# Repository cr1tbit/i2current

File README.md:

# I2Current powerboard

The Raison d'être of this board is to be a powerful, extensible, and affordable replacement for hotglueing a random powerbank into your next portable small-scale electronic project.

The largest benefit comes from the I2C interface - If, for example, a Raspberry Pi is powered with this board, it can actually check the battery state, if DC-jack is currently charging the device, or even see the power draw of other peripherals connected to this system.

The board is most useful for powering devices requiring peak power draw between 15W-60W.

For devices requiring less power, the cost overhead becomes a bit too much - alternative solutions on aliexpress, albeit not as much versatile, can cost less than $3 (this board costs ~$10, ordering 20 units from JLCPCB).

## Sub-components

### BQ25792 Li-Ion charger

Specs:

* 3.6-24V input, max 3A (realistically, ~60W)
* Input voltage independent from battery pack (buck-boost built-in)
* Input from USB-C and/or DC barrel jack.
* Can provide up to 3.33A@20V output to the same USB-C port
* can work with 1S-4S (cells in series)
* output current 5A (with 4 cells (~16V), up to ~80W output)
* Works properly without battery pack too (can work as buck-boost power supply)
* Many parameters configurable via i2c
* Various battery/input/output voltages/currents readout

This charger is incredibly universal, costing around 1$ it provides versatility for many types of projects.

### TPS56637 5V output step-down converter

It can provide up to 6A (30W) on output. However, it requires atleast 2S packet to be usable.

### MT2492 3V3 DC-DC

This converter supports optional built-in ESP32-C3 controller, and can also be accesed via output pins

### SPX3819M5-L-3-3 3V3 LDO

This low-power stabilizer provides power to onboard devices and some circuitry. It cannot be turned off, in contrast to 2 other converters.

### FUSB302B Power Delivery controller

This device is controlled via i2c, and can be used to negotiate up to 5A/20V from compatible USB-C chargers.

Arduino library is available.

## Connectors

### Output 2.54 connector

This connector has been designed for low-profile goldpin socket connector (the male header actually goes through the holes in the PCB)

Shield can be designed, utilizing this connector.

### Picoblade connector

This connector is dedicated for devices, where a "master" board sits somewhere else in the system. 

### Battery connector

* Battery input
* NTC resistor input (every battery pack should contain one, more on that later)
* GND
* Battery output (coming from BQ charger, provides stable voltage when baterry is depleated or missing)
* GLOB_OFF (pin for external power-off switch)
* VDC_IN (same as from barrel jack input)

## More to come...

this board has many more fun quirks - I'll describe more details at a later date.

* optional mini front panel with OLED
* Passive-PoE input
* standalone 4-channel WLED controller
* USB data lanes passthrough for 2 connectors and built-in ESP32

#### Todo - document:

* Li-ion safety guide
* USB passthrough
* GLOB_OFF usage
* Pinout description for every connector
* 1S-4S config and limitations

## Sponsors

Developent of this board is supported by [Clue.lamp](https://www.instagram.com/clue.lamp/).

Check them out, the device looks really nice, and utilizes state-of-the-art electronic design for both wired and wireless usage :)

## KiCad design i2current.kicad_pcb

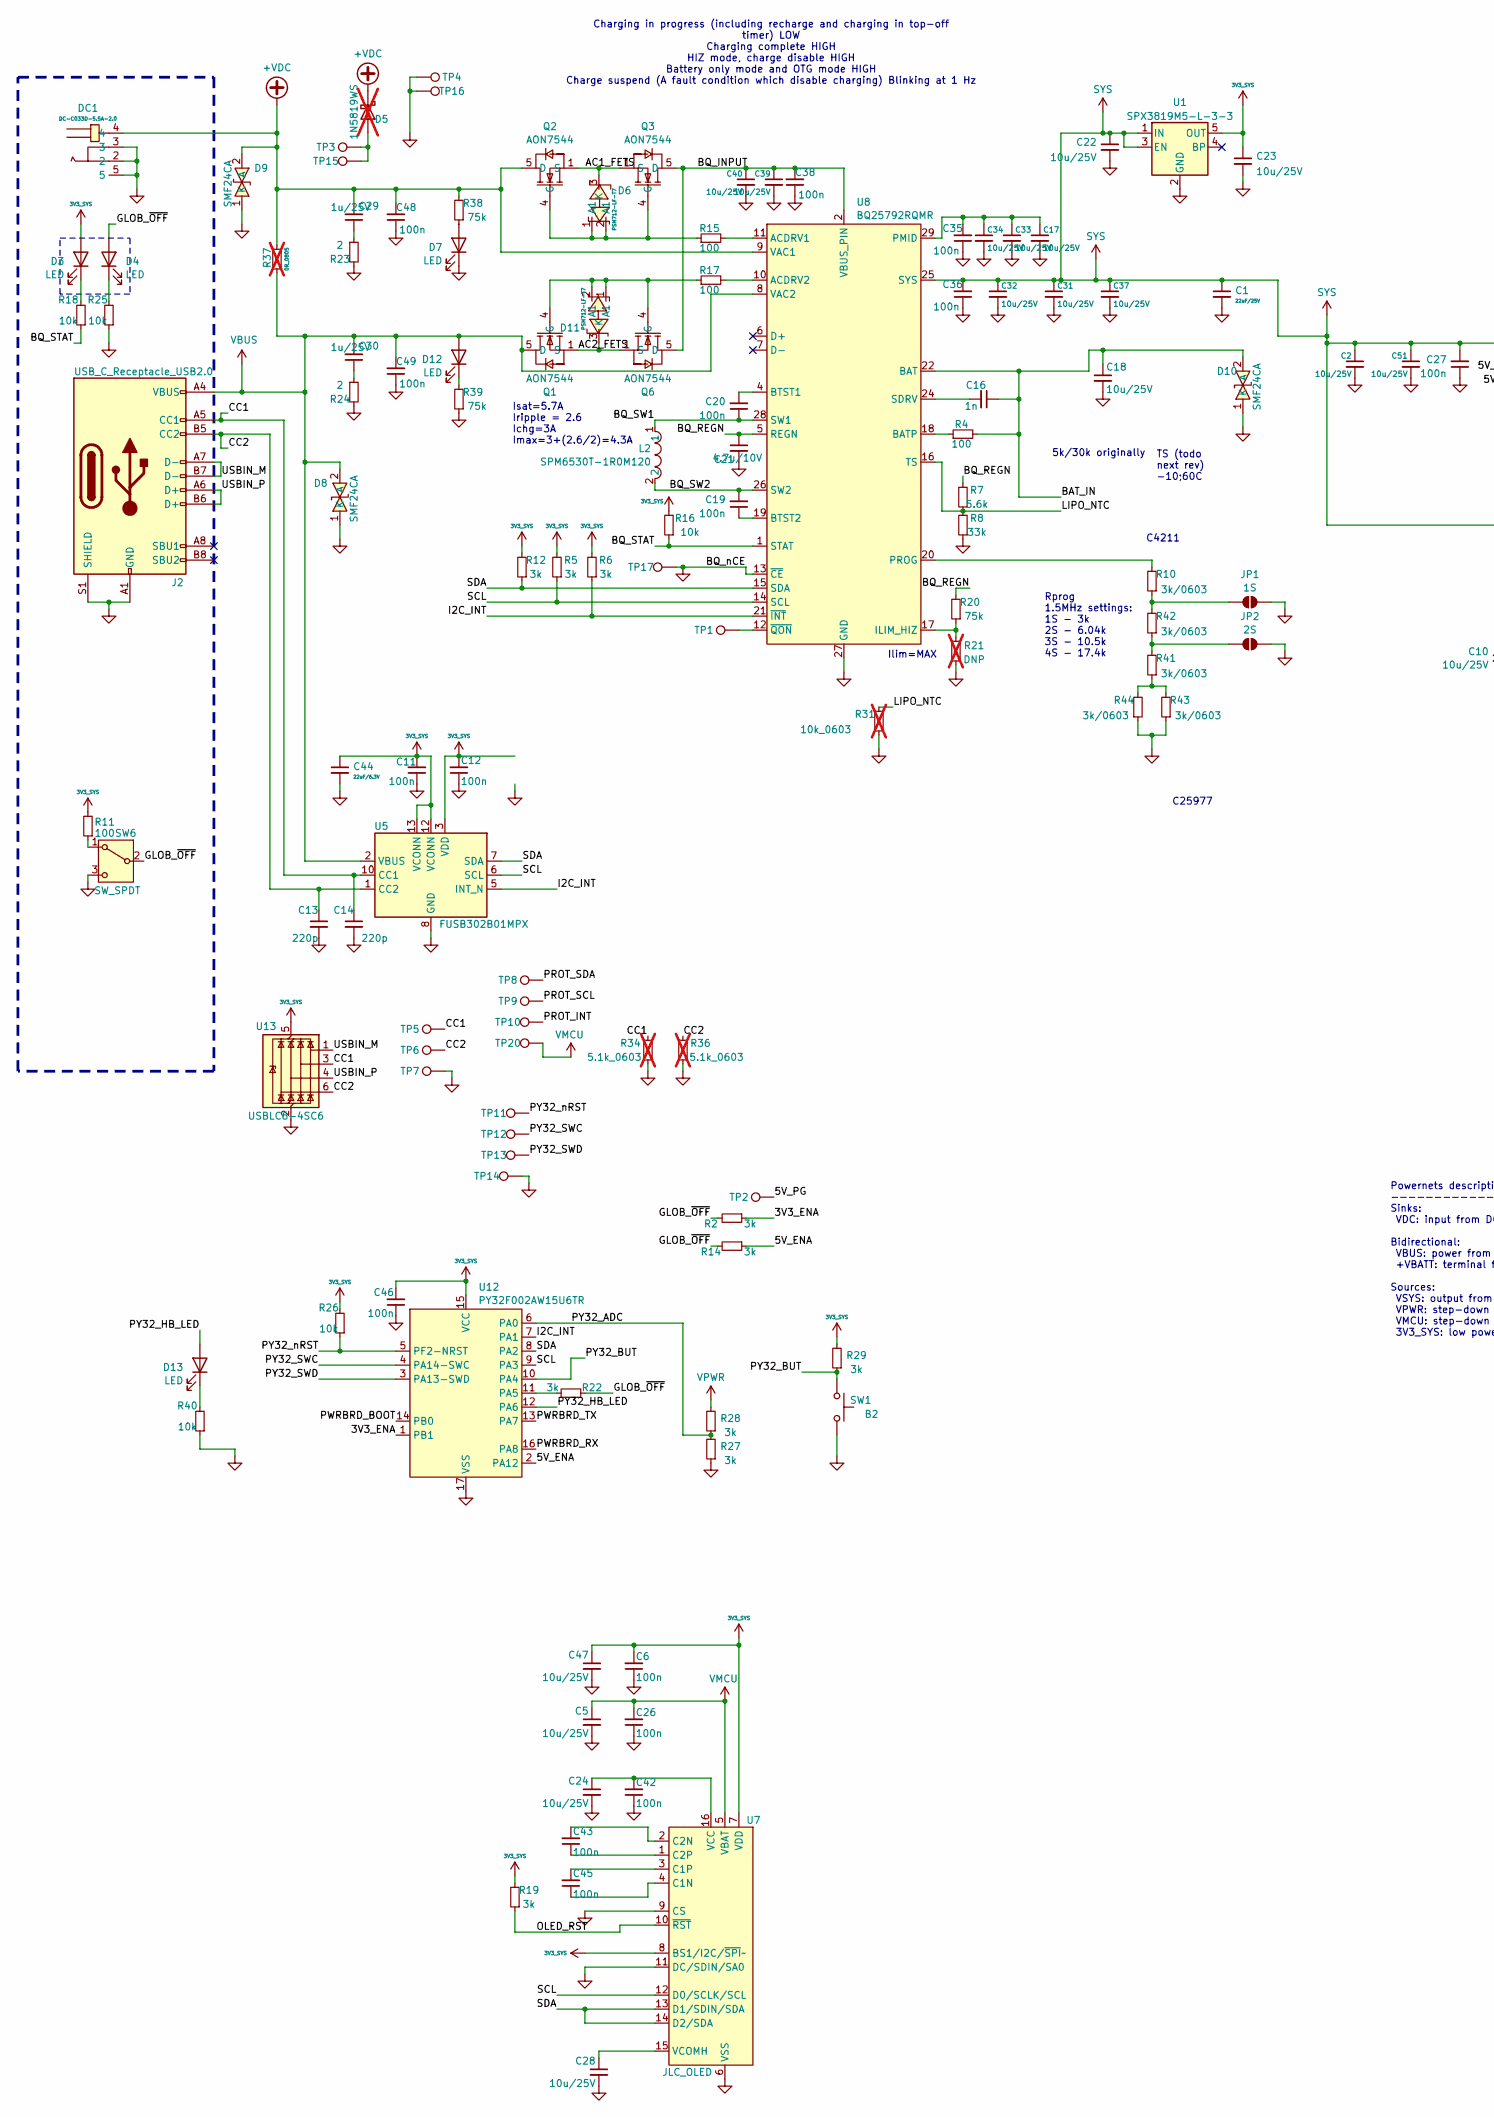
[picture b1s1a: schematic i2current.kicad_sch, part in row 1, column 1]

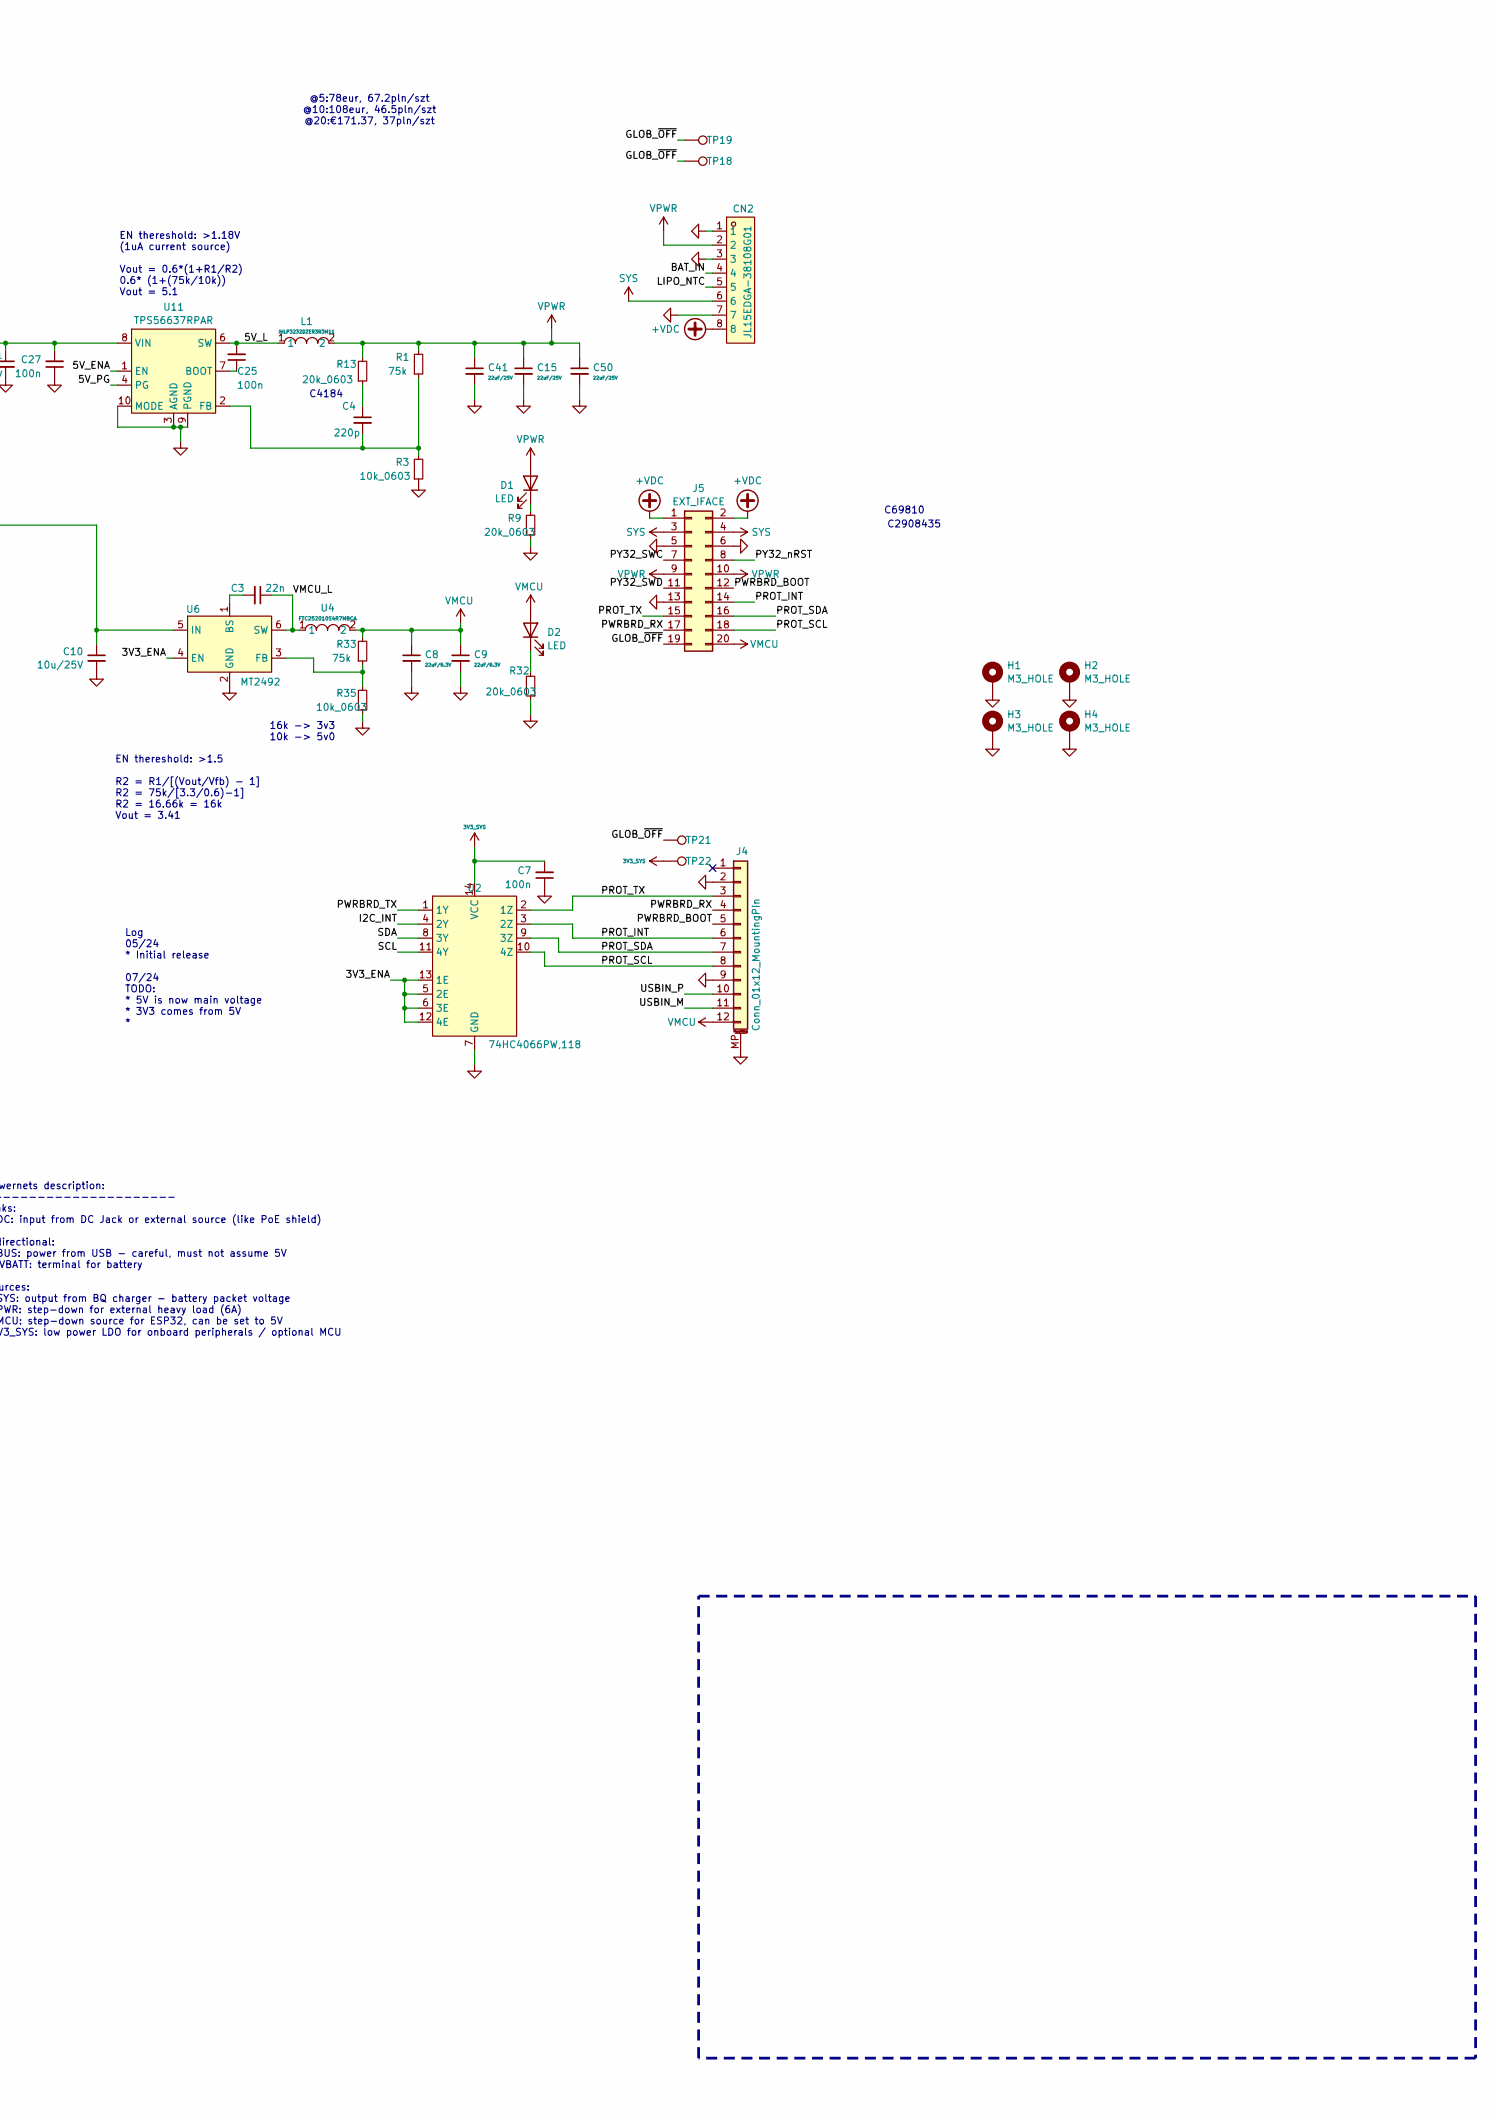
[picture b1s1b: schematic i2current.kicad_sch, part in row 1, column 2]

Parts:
C1, C15, C41, C50: 22uF/25V; C_1206_3216Metric; LCSC C12891
C2, C5, C10, C17, C18, C22, C23, C24, C28, C31, C32, C33, C34, C37, C39, C40, C47, C51: 10u/25V; C_0603_1608Metric; LCSC C96446
C3: 22n; C_0402_1005Metric; LCSC C1532
C4, C13, C14: 220p; C_0402_1005Metric; LCSC C1530
C6, C7, C11, C12, C19, C20, C25, C26, C27, C35, C36, C38, C42, C43, C45, C46, C48, C49: 100n; C_0402_1005Metric; LCSC C307331
C8, C9, C44: 22uF/6.3V; C_0603_1608Metric; LCSC C59461
C16: 1n; C_0402_1005Metric; LCSC C1532
C21: 4.7u/10V; C_0402_1005Metric; LCSC C23733
C29, C30: 1u/25V; C_0603_1608Metric; LCSC C15849
CN2: JL15EDGA-38108G01; CONN-TH_8P-P3.81_JILN_JL15EDGA-38108G01; LCSC Part C2908436
D1, D2, D3, D4, D7, D12, D13: LED; LED_0603_1608Metric; LCSC C72038
D5: 1N5819WS; D_SOD-323; LCSC C191023; not fitted
D6, D11: PSM712-LF-T7; SOT-23-3_L3.0-W1.7-P0.95-LS2.9-BR; LCSC C32677
D8, D9, D10: SMF24CA; SOD-123FL_L2.7-W1.8-LS3.8-BI; LCSC C19077515
DC1: DC-C033D-5.5A-2.0; DC-IN-TH_DC-C033D-5.5A-2.5; LCSC C500113
H1, H2, H3, H4: M3_HOLE; MountingHole_3.2mm_LONGE
J2: USB_C_Receptacle_USB2.0; USB_C_Receptacle_HRO_TYPE-C-31-M-12; LCSC C165948
J4: Conn_01x12_MountingPin; Molex_PicoBlade_53261-1271_1x12-1MP_P1.25mm_Horizontal; LCSC C276921
J5: EXT_IFACE; SAMTEC_HLE-110-02-F-DV-BE-A
JP1: 1S; SolderJumper-2_P1.3mm_Open_TrianglePad1.0x1.5mm
JP2: 2S; SolderJumper-2_P1.3mm_Open_TrianglePad1.0x1.5mm
L1: IHLP3232DZER3R3M11; IND-SMD_L8.7-W8.2_IHLP-3232CZ; LCSC C511015
L2: SPM6530T-1R0M120; IND-SMD_L7.1-W6.5-P5.60; LCSC C87572
Q1, Q2, Q3, Q6: AON7544; DFN-8_L3.3-W3.3-P0.65-BL-2; LCSC C315567
R1, R20, R33, R38, R39: 75k; R_0603_1608Metric
R2, R5, R6, R12, R14, R19, R22, R27, R28, R29: 3k; R_0402_1005Metric
R3, R35: 10k_0603; R_0603_1608Metric
R4, R11, R15, R17: 100; R_0402_1005Metric
R7: 5.6k; R_0603_1608Metric
R8: 33k; R_0603_1608Metric
R9, R13, R32: 20k_0603; R_0603_1608Metric
R10, R41, R42, R43, R44: 3k/0603; R_0603_1608Metric
R16, R18, R25, R26, R40: 10k; R_0402_1005Metric
R21: DNP; R_0603_1608Metric; not fitted
R23, R24: 2; R_0603_1608Metric; LCSC C22939
R31: 10k_0603; R_0603_1608Metric; not fitted
R34, R36: 5.1k_0603; R_0603_1608Metric; not fitted
R37: 0R_0805; R_0805_2012Metric; not fitted
SW1: B2; SW_SPST_TL3342; LCSC C318884
SW6: SW_SPDT; SW_Slide_SPDT_Angled_CK_OS102011MA1Q; LCSC C393937
TP1, TP17, TP18, TP19, TP21, TP22: TestPoint; Nano_testpad_0.5x1.0mm
TP2, TP5, TP6, TP7, TP8, TP9, TP10, TP11, TP12, TP13, TP14, TP20: TestPoint; TestPoint_Pad_D1.0mm
TP3, TP4, TP15, TP16: TestPoint; TestPoint_Pad_D2.0mm
U1: SPX3819M5-L-3-3; SOT-23-5; LCSC C9055
U2: 74HC4066PW,118; TSSOP-14_L5.0-W4.4-P0.65-LS6.4-BL; LCSC C5650
U4: FTC252010S4R7MBCA; IND-SMD_L2.5-W2.0-VLS252012CX-150M; LCSC C5832360
U5: FUSB302B01MPX; WQFN-14-1EP_2.5x2.5mm_P0.5mm_EP1.45x1.45mm; LCSC C442699
U6: MT2492; SOT-23-6_L2.9-W1.6-P0.95-LS2.8-BL; LCSC C89358
U7: JLC_OLED; OLED-042-JLC
U8: BQ25792RQMR; QFN-29_L4.0-W4.0-P0.40-TL-BQ25792RQMR; LCSC C2862876
U11: TPS56637RPAR; VQFN-HR-10_L3.0-W3.0_RPA; LCSC C841386
U12: PY32F002AW15U6TR; TQFN-16-1EP_3x3mm_P0.5mm_EP1.6x1.6mm; LCSC C5291740
U13: USBLC6-4SC6; SOT-23-6; LCSC C5197386

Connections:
3V3_SYS: C6.2, C7.2, C11.2, C12.2, C23.1, C44.1, C46.2, C47.1, D3.2 (A), R5.2, R6.2, R11.2, R12.2, R16.2, R19.2, R26.2, R29.2, TP22.1, U1.5 (OUT), U2.14 (VCC), U5.3 (VDD), U5.4 (VDD), U5.12 (VCONN), U5.13 (VCONN), U7.7 (VDD), U7.8 (BS1/I2C/~SPI~), U12.15 (VCC), U13.5 (VBUS)
+VDC: C29.2, C48.2, CN2.8, D5.1 (K), D9.2 (A), DC1.4, J5.1, J5.2, Q2.5 (D), R37.1, R38.2, U8.9 (VAC1)
/3V3_ENA: R2.1, U2.5 (2E), U2.6 (3E), U2.12 (4E), U2.13 (1E), U6.4 (EN), U12.1 (PB1)
/5V_ENA: R14.1, U11.1 (EN), U12.2 (PA12)
/5V_L: C25.2, L1.1, U11.6 (SW)
/5V_PG: TP2.1, U11.4 (PG)
/AC1_FETS: D6.3 (K), Q2.1 (S), Q2.2 (S), Q2.3 (S), Q3.1 (S), Q3.2 (S), Q3.3 (S)
/AC2_FETS: D11.3 (K), Q1.1 (S), Q1.2 (S), Q1.3 (S), Q6.1 (S), Q6.2 (S), Q6.3 (S)
/BQ_REGN: C21.1, R7.2, R20.2, U8.5 (REGN)
/BQ_STAT: R16.1, R18.1, U8.1 (STAT)
/BQ_SW1: C20.1, L2.1, U8.28 (SW1)
/BQ_SW2: C19.2, L2.2, U8.26 (SW2)
/CC1: C14.1, J2.A5 (CC1), R34.1, TP5.1, U5.10 (CC1), U5.11 (CC1), U13.3 (I/O2)
/CC2: C13.1, J2.B5 (CC2), R36.1, TP6.1, U5.1 (CC2), U5.14 (CC2), U13.6 (I/O4)
/GLOB_~OFF: D4.2 (A), J5.19, R2.2, R14.2, R22.2, SW6.2 (B), TP18.1, TP19.1, TP21.1
/I2C_INT: R6.1, U2.4 (2Y), U5.5 (INT_N), U8.21 (~INT), U12.7 (PA1)
/LIPO_NTC: CN2.5, R7.1, R8.2, R31.2, U8.16 (TS)
/OLED_RST: R19.1, U7.10 (~RST)
/PROT_INT: J4.6, J5.14, TP10.1, U2.3 (2Z)
/PROT_SCL: J4.8, J5.18, TP9.1, U2.10 (4Z)
/PROT_SDA: J4.7, J5.16, TP8.1, U2.9 (3Z)
/PROT_TX: J4.3, J5.15, U2.2 (1Z)
/PWRBRD_BOOT: J4.5, J5.12, U12.14 (PB0)
/PWRBRD_RX: J4.4, J5.17, U12.16 (PA8)
/PWRBRD_TX: U2.1 (1Y), U12.13 (PA7)
/PY32_ADC: R27.2, R28.1, U12.6 (PA0)
/PY32_BUT: R29.1, SW1.2, U12.10 (PA4)
/PY32_HB_LED: D13.2 (A), U12.12 (PA6)
/PY32_SWC: J5.7, TP12.1, U12.4 (PA14-SWC)
/PY32_SWD: J5.11, TP13.1, U12.3 (PA13-SWD)
/PY32_nRST: J5.8, R26.1, TP11.1, U12.5 (PF2-NRST)
/SCL: R5.1, U2.11 (4Y), U5.6 (SCL), U7.12 (D0/SCLK/SCL), U8.14 (SCL), U12.9 (PA3)
/SDA: R12.1, U2.8 (3Y), U5.7 (SDA), U7.13 (D1/SDIN/SDA), U7.14 (D2/SDA), U8.15 (SDA), U12.8 (PA2)
/USBIN_M: J2.A7 (D-), J2.B7 (D-), J4.11, U13.1 (I/O1)
/USBIN_P: J2.A6 (D+), J2.B6 (D+), J4.10, U13.4 (I/O3)
/VMCU_L: C3.1, U4.1, U6.6 (SW)
BAT: C16.1, C18.1, CN2.4, D10.2 (A), R4.2, U8.22 (BAT), U8.23 (BAT)
GND: C1.2, C2.2, C5.2, C6.1, C7.1, C8.2, C9.2, C10.2, C11.1, C12.1, C13.2, C14.2, C15.2, C17.2, C18.2, C21.2, C22.2, C23.2, C24.2, C26.1, C27.1, C28.2, C31.2, C32.2, C33.2, C34.2, C35.1, C36.1, C37.2, C38.1, C39.2, C40.2, C41.2, C42.1, C44.2, C46.1, C47.2, C48.1, C49.1, C50.2, C51.2, CN2.1, CN2.3, CN2.7, D7.1 (K), D8.1 (K), D9.1 (K), D10.1 (K), DC1.2, DC1.3, DC1.5, H1.1, H2.1, H3.1, H4.1, J2.A1 (GND), J2.A12 (GND), J2.B1 (GND), J2.B12 (GND), J2.S1 (SHIELD), J4.2, J4.9, J4.MP (MountPin), J5.5, J5.6, J5.13, JP1.2 (B), JP2.2 (B), R3.1, R8.1, R9.1, R21.1, R23.2, R24.2, R25.1, R27.1, R31.1, R32.1, R34.2, R35.1, R36.2, R39.1, R40.1, R43.1, R44.1, SW1.1, SW6.3 (C), TP4.1, TP7.1, TP14.1, TP16.1, TP17.1, U1.2 (GND), U2.7 (GND), U5.8 (GND), U5.9 (GND), U5.15 (GND), U6.2 (GND), U7.6 (VSS), U7.9 (CS), U7.11 (DC/SDIN/SA0), U8.13 (~CE), U8.27 (GND), U11.3 (AGND), U11.9 (PGND), U11.10 (MODE), U12.17 (VSS), U13.2 (GND)
unnamed: C4.1, R13.1
unnamed: C29.1, R23.1
unnamed: C30.1, R24.1
unnamed: D1.1 (K), R9.2
unnamed: D2.1 (K), R32.2
unnamed: D3.1 (K), R18.2
unnamed: D4.1 (K), R25.2
unnamed: D5.2 (A), TP3.1, TP15.1
unnamed: D7.2 (A), R38.1
unnamed: D12.1 (K), R39.2
unnamed: D13.1 (K), R40.2
unnamed: JP1.1 (A), R10.1, R42.2
unnamed: JP2.1 (A), R41.2, R42.1
unnamed: D11.1 (A1), D11.2 (A1), Q1.4 (G), Q6.4 (G), R17.1
unnamed: D6.1 (A1), D6.2 (A1), Q2.4 (G), Q3.4 (G), R15.1
unnamed: R41.1, R43.2, R44.2
unnamed: R11.1, SW6.1 (A)
unnamed: C3.2, U6.1 (BS)
unnamed: R33.1, R35.2, U6.3 (FB)
unnamed: C45.1, U7.4 (C1N)
unnamed: C45.2, U7.3 (C1P)
unnamed: C43.2, U7.2 (C2N)
unnamed: C43.1, U7.1 (C2P)
unnamed: C24.1, C42.2, U7.16 (VCC)
unnamed: C28.1, U7.15 (VCOMH)
unnamed: R15.2, U8.11 (ACDRV1)
unnamed: R17.2, U8.10 (ACDRV2)
unnamed: R4.1, U8.18 (BATP)
unnamed: C20.2, U8.4 (BTST1)
unnamed: C19.1, U8.19 (BTST2)
unnamed: R20.1, R21.2, U8.17 (ILIM_HIZ)
unnamed: C17.1, C33.1, C34.1, C35.2, U8.29 (PMID)
unnamed: R10.2, U8.20 (PROG)
unnamed: C16.2, U8.24 (SDRV)
unnamed: TP1.1, U8.12 (~QON)
unnamed: C25.1, U11.7 (BOOT)
unnamed: C4.2, R1.1, R3.2, U11.2 (FB)
unnamed: R22.1, U12.11 (PA5)
SYS: C1.1, C2.1, C10.1, C22.1, C27.2, C31.1, C32.1, C36.2, C37.1, C51.1, CN2.6, J5.3, J5.4, U1.1 (IN), U1.3 (EN), U6.5 (IN), U8.25 (SYS), U11.8 (VIN)
VBUS: C30.2, C49.2, D8.2 (A), D12.2 (A), J2.A4 (VBUS), J2.A9 (VBUS), J2.B4 (VBUS), J2.B9 (VBUS), Q1.5 (D), R37.2, U5.2 (VBUS), U8.8 (VAC2)
VBUS_PIN: C38.2, C39.1, C40.1, Q3.5 (D), Q6.5 (D), U8.2 (VBUS_PIN), U8.3 (VBUS_PIN)
VMCU: C5.1, C8.1, C9.1, C26.2, D2.2 (A), J4.12, J5.20, R33.2, TP20.1, U4.2, U7.5 (VBAT)
VPWR: C15.1, C41.1, C50.1, CN2.2, D1.2 (A), J5.9, J5.10, L1.2, R1.2, R13.2, R28.2

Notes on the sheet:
C2908435
C4184
16k -> 3v3 10k -> 5v0
C69810
Log 05/24 * Initial release 07/24 TODO: * 5V is now main voltage * 3V3 comes from 5V *
C25977
EN thereshold: >1.18V (1uA current source) Vout = 0.6*(1+R1/R2) 0.6* (1+(75k/10k)) Vout = 5.1
EN thereshold: >1.5 R2 = R1/[(Vout/Vfb) - 1] R2 = 75k/[3.3/0.6)-1] R2 = 16.66k = 16k Vout = 3.41
Isat=5.7A Iripple = 2.6 Ichg=3A Imax=3+(2.6/2)=4.3A
Powernets description: ---------------------- Sinks: VDC: input from DC Jack or external source (like PoE shield) Bidirectional: VBUS: power from USB - careful, must not assume 5V +VBATT: terminal for battery Sources: VSYS: output from BQ charger - battery packet voltage VPWR: step-down for externa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
Charging in progress (including recharge and charging in top-off timer) LOW Charging complete HIGH HIZ mode, charge disable HIGH Battery only mode and OTG mode HIGH Charge suspend (A fault condition which disable charging) Blinking at 1 Hz
Rprog 1.5MHz settings: 1S - 3k 2S - 6.04k 3S - 10.5k 4S - 17.4k
@5:78eur, 67.2pln/szt @10:108eur, 46.5pln/szt @20:€171.37, 37pln/szt
5k/30k originally
C4211
Ilim=MAX
TS (todo next rev) -10;60C

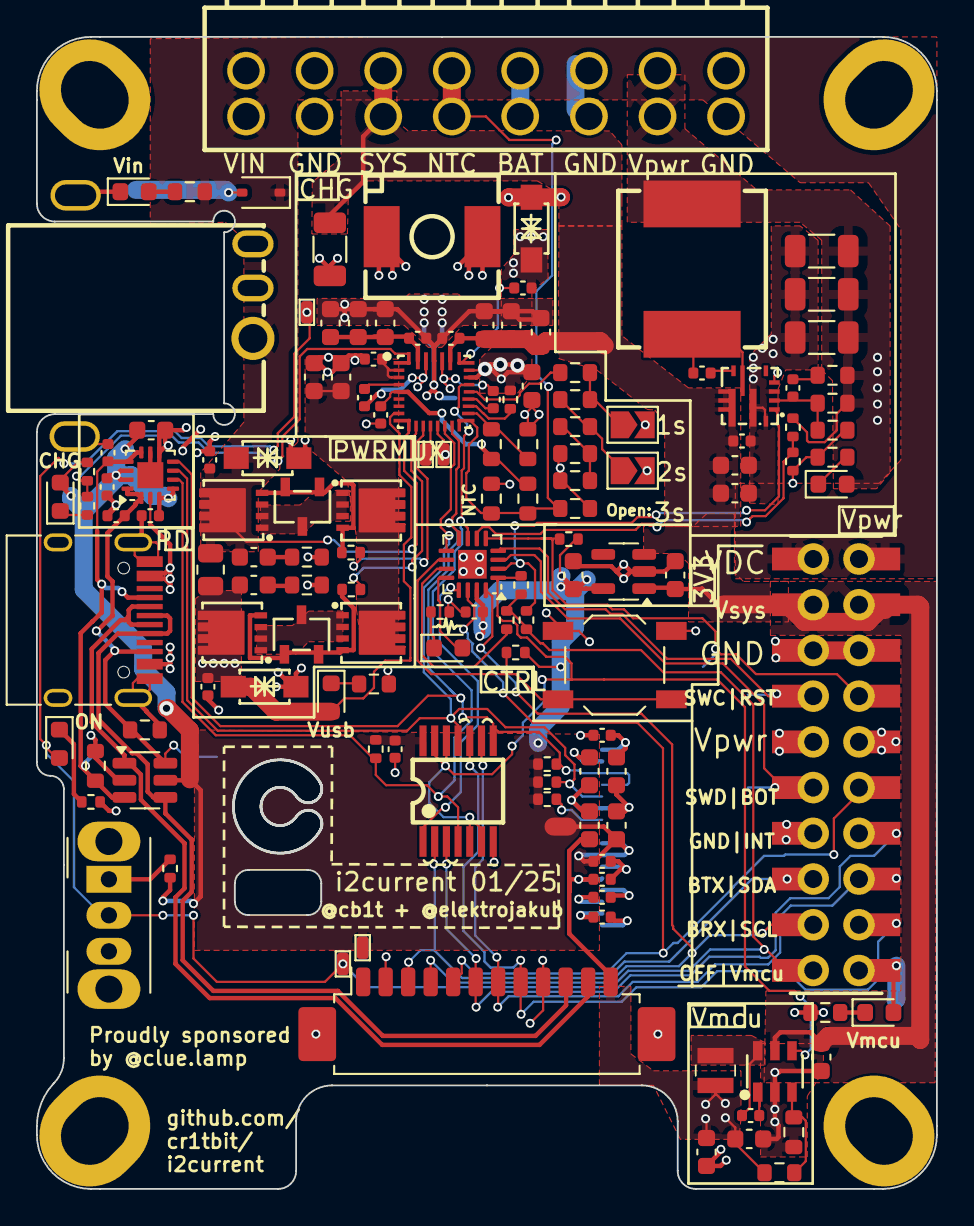
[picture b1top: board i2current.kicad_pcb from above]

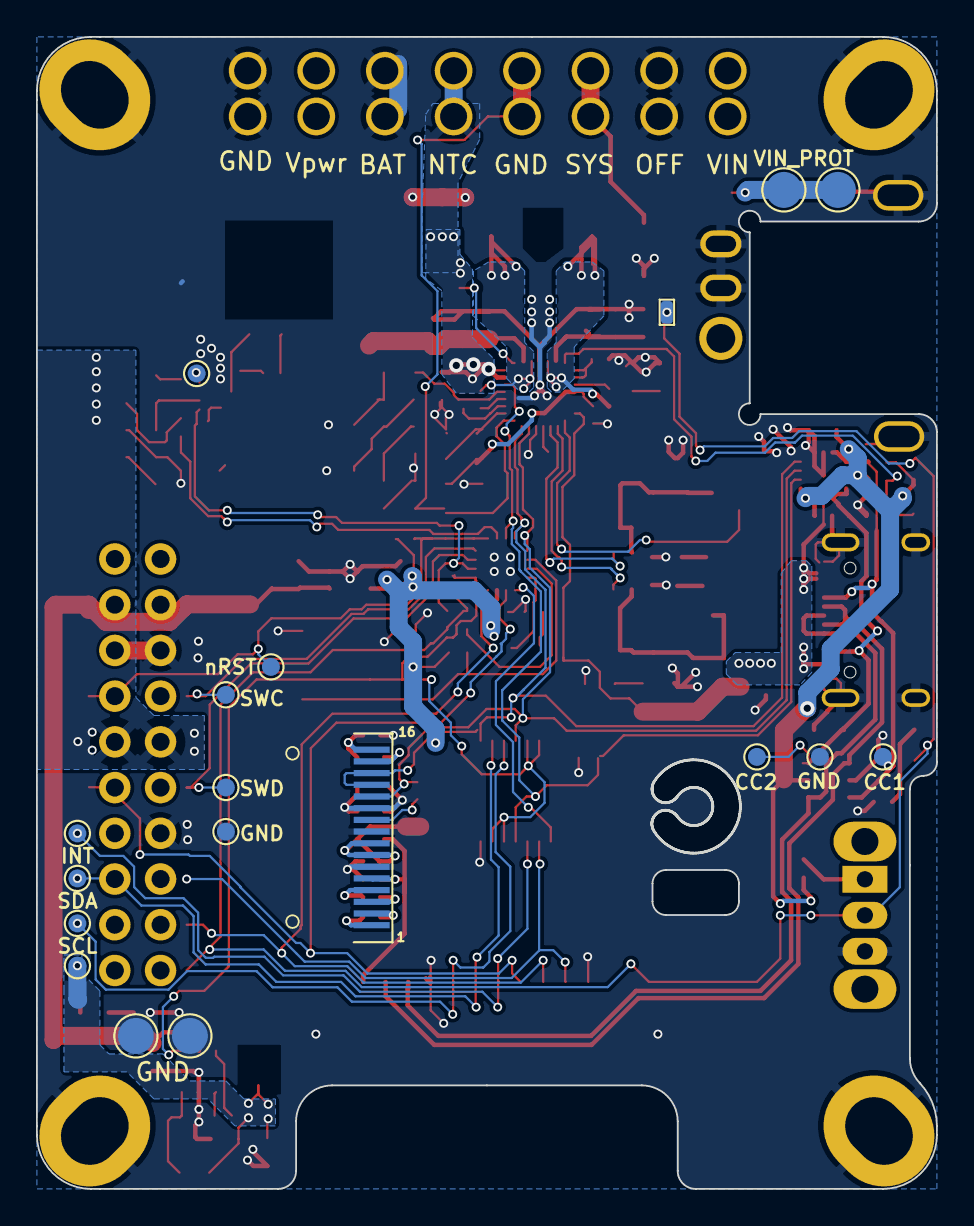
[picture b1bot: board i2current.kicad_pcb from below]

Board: 2 copper layers, 50.0 x 64.0 mm, 158 parts (18 on the bottom side), 81 nets.

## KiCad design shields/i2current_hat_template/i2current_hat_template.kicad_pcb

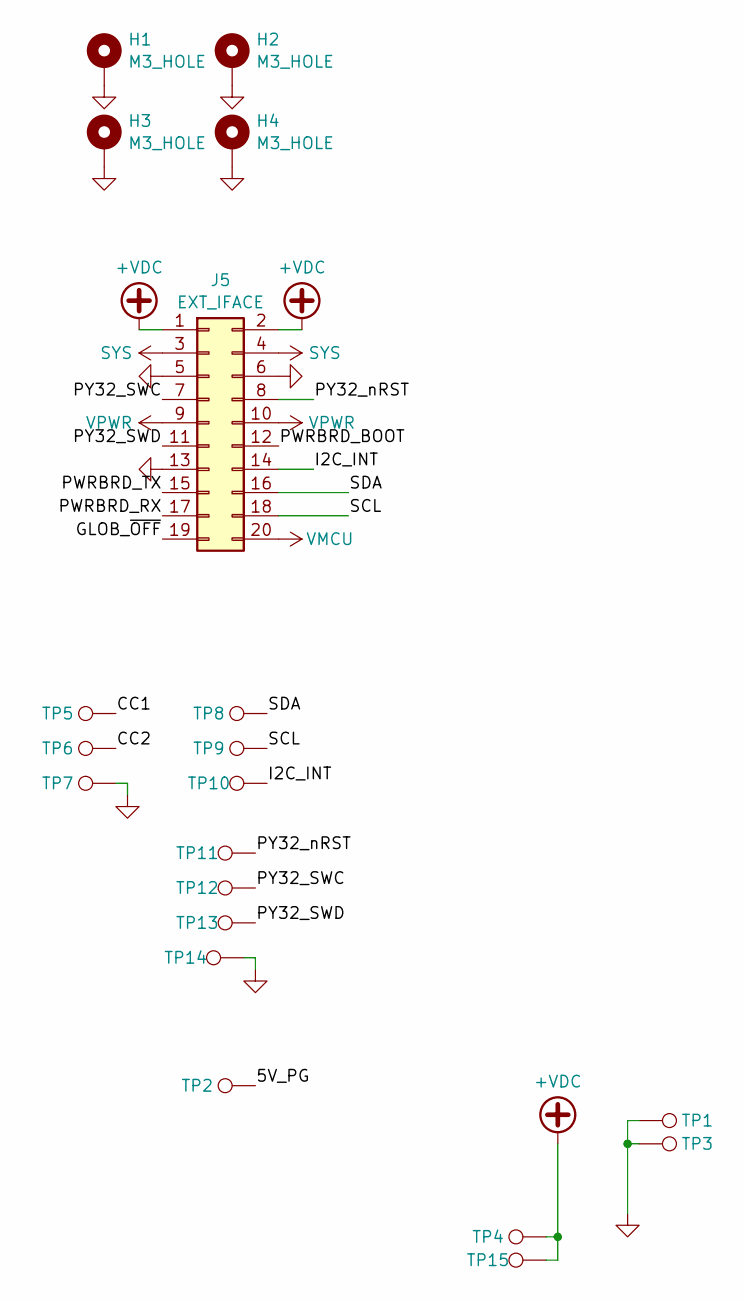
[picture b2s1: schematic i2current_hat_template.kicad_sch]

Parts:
H1, H2, H3, H4: M3_HOLE; MountingHole_3.2mm_M3_DIN965_Pad
J5: EXT_IFACE; PinHeader_2x10_P2.54mm_Vertical
TP1, TP3, TP4, TP15: TestPoint; TestPoint_Pad_D2.0mm
TP2, TP5, TP6, TP7, TP8, TP9, TP10, TP11, TP12, TP13, TP14: TestPoint; TestPoint_Pad_D1.0mm

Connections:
+VDC: J5.1, J5.2, TP4.1, TP15.1
/5V_PG: TP2.1
/CC1: TP5.1
/CC2: TP6.1
/GLOB_~OFF: J5.19
/I2C_INT: J5.14, TP10.1
/PWRBRD_BOOT: J5.12
/PWRBRD_RX: J5.17
/PWRBRD_TX: J5.15
/PY32_SWC: J5.7, TP12.1
/PY32_SWD: J5.11, TP13.1
/PY32_nRST: J5.8, TP11.1
/SCL: J5.18, TP9.1
/SDA: J5.16, TP8.1
GND: H1.1, H2.1, H3.1, H4.1, J5.5, J5.6, J5.13, TP1.1, TP3.1, TP7.1, TP14.1
SYS: J5.3, J5.4
VMCU: J5.20
VPWR: J5.9, J5.10

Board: 2 copper layers, 20 parts (0 on the bottom side), 10 nets, no tracks yet.

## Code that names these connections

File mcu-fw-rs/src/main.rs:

#![no_std]
#![no_main]
#![feature(type_alias_impl_trait)]
#![feature(impl_trait_in_assoc_type)]

use defmt::*;
use embassy_executor::Spawner;

#[allow(unused)]
use embassy_time::{Duration, Timer, Ticker, Instant};

#[allow(unused)]
use py32_hal::{
    adc::{Adc, SampleTime},
    gpio::{Level, Pull, Speed},
    peripherals::{ADC, I2C1, USART1, PA0, PA1, PA2, PA3, PA4, PA5, PA6, PA7, PA8, PA12, PA13, PA14, PB0, PB1},
};
use {defmt_rtt as _, panic_probe as _};

// use cortex_m::peripheral::SCB;
use cortex_m_rt::{exception, ExceptionFrame};

mod bsp;
use bsp::pins::Board;
// use bsp::interrupts::Irqs;

#[embassy_executor::main]
async fn main(_spawner: Spawner) {
    info!("Hello World!");
    // Initialize board
    let mut board = Board::init();

    // Initialize battery monitor
    // let bat_monitor = bsp::bat::BatteryMonitor::new(board.adc, board.pins.pa0);

    // // Spawn battery monitor task
    // spawner.spawn(bsp::bat::run_bat_monitor(bat_monitor)).unwrap();

    board.i2c.scan();

    // Main loop
    let mut ticker = Ticker::every(Duration::from_secs(1));
    loop {
        ticker.next().await;
        info!("Tick");
    }
}

#[exception]
unsafe fn HardFault(_ef: &ExceptionFrame) -> ! {
    defmt::panic!("HardFault");
}

#[exception]
unsafe fn DefaultHandler(_irq: i16) {
    defmt::panic!("Unhandled exception ");
}

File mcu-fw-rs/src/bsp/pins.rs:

// Please note, this code has been EXTREMELY vibecoded, and looks like shit.
// I only tested GPIO for now. Putting it on the repo for reference.

use py32_hal::{
    adc::{Adc, SampleTime},
    gpio::{Flex, Level, Pull, Speed},
    peripherals::ADC,
    rcc::{Pll, PllSource, Sysclk},
    time::Hertz,
    Peripheral, Peripherals,
};

use crate::bsp::{
    i2c::{I2cPeripheral},
    interrupts::Irqs,
};

/// Board Support Package for the PY32 MCU
#[allow(unused)]
pub struct Board<'a> {
    /// ADC peripheral
    pub adc: Adc<'a, ADC>,
    /// I2C peripheral
    pub i2c: I2cPeripheral<'a>,
    /// Available GPIO pins
    pub pins: ControlPins,
}

/// SWD debug pins
#[allow(unused)]
pub struct SwdPins {
    /// SWDIO pin
    pub swdio: Flex<'static>,
    /// SWCLK pin
    pub swclk: Flex<'static>,
}

// /// PA0 - ADC input
// /// PA1 - I2C interrupt
// /// PA2 - I2C SDA
// /// PA3 - I2C SCL
// /// PA4 - Battery charger chip select
// /// PA5 - OLED reset
// /// PA6 - Global power off
// /// PA7 - Power board UART TX
// /// PA8 - Power board UART RX
// /// PA12 - 5V enable
// /// PB0 - Power board boot
// /// PB1 - 3.3V enable

/// Available GPIO pins
#[allow(unused)]
pub struct ControlPins {
    pub chg_cs: Flex<'static>,   //CS
    pub oled_rst: Flex<'static>, //OLED rst
    pub glob_off: Flex<'static>, //GLOB_OFF
    pub ena_5v: Flex<'static>,   //5V ENA
    pub ena_3v3: Flex<'static>,  //3v3 ENA
}

impl<'a> Board<'a> {
    pub fn get_periph_handle() -> Peripherals {
        let mut cfg: py32_hal::Config = Default::default();
        cfg.rcc.hsi = Some(Hertz::mhz(24));
        cfg.rcc.pll = Some(Pll {
            src: PllSource::HSI,
        });
        cfg.rcc.sys = Sysclk::PLL;

        py32_hal::init(cfg)
    }

    /// Initialize the board and its peripherals
    pub fn init() -> Self {
        let p = Self::get_periph_handle();

        // Initialize GPIO pins
        let pins = ControlPins {
            chg_cs: Flex::new(p.PA4),
            oled_rst: Flex::new(p.PA5),
            glob_off: Flex::new(p.PA6),
            ena_5v: Flex::new(p.PA12),
            ena_3v3: Flex::new(p.PB1),
        };
        unsafe {
            // Initialize ADC
            let mut adc = Adc::new(p.ADC, Irqs);
            adc.set_sample_time(SampleTime::CYCLES71_5);

            // Initialize I2C
            let i2c = I2cPeripheral::new(
                p.I2C1,
                p.PA2.clone_unchecked(),
                p.PA3.clone_unchecked(),
                p.PA1.clone_unchecked(),
            );

            Self { adc, i2c, pins }
        }
    }
}

/// Helper functions for configuring pins
#[allow(unused)]
impl ControlPins {
    /// Configure a pin as output
    pub fn configure_output(&mut self, pin: &mut Flex<'static>, level: Level) {
        pin.set_as_output(Speed::VeryHigh);
        match level {
            Level::High => pin.set_high(),
            Level::Low => pin.set_low(),
        }
    }

    /// Configure a pin as input
    pub fn configure_input(&mut self, pin: &mut Flex<'static>, pull: Pull) {
        pin.set_as_input(pull);
    }
}

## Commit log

2024-03-24 add files
2024-04-12 save before charger replace
2024-04-23 connector placement
2024-04-28 adadadadadadadadadada
2024-05-04 do backup kids
2024-05-05 backup 2
2024-05-05 unratnestd'd
2024-05-11 routing 2
2024-05-12 work
2024-05-13 kinda finish route, needs some checks still
2024-05-18 i start order
2024-06-19 05/24 order
2024-06-19 add testing firmware (not tested yet)
2024-08-02 start order
2024-08-31 add fw update
2024-09-24 add documentation
2024-09-24 add readme and pics
2024-09-24 more readme
2024-09-24 bottom text
2024-09-24 remove unused schematic file
2024-10-03 add SD support
2024-10-03 add SD test
2025-01-06 checkpoint for next rev
2025-01-07 finish DRC
2025-01-10 before parts
2025-01-11 really before order really
2025-01-12 01/25 order
2025-01-12 add test FW changes
2025-01-12 add hat template
2025-03-15 Finish PoC BQ + Oled features
2025-04-15 add i2current MCU rust FW PoC
2025-04-16 I2C scanner
2025-04-20 bit of BSP cleanup
2025-04-22 PCB next rev checkpoint
2025-05-29 may order
2025-12-16 fix firmware tests for other devs
2025-12-16 fix PD IC serial output not working with esp32
